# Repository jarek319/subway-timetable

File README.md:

# subway-timetable
A "Times Square" colorful LED display that shows you your favorite subway's status

Up to date info about your subway line and its arrival time for your station

I wanted to use one of those super colorful 32 x 64 RGB LED "times square" modules to display the subway schedule of the train nearest to me.

Still a work in progress, but the hardware is ready and the firmware works :)

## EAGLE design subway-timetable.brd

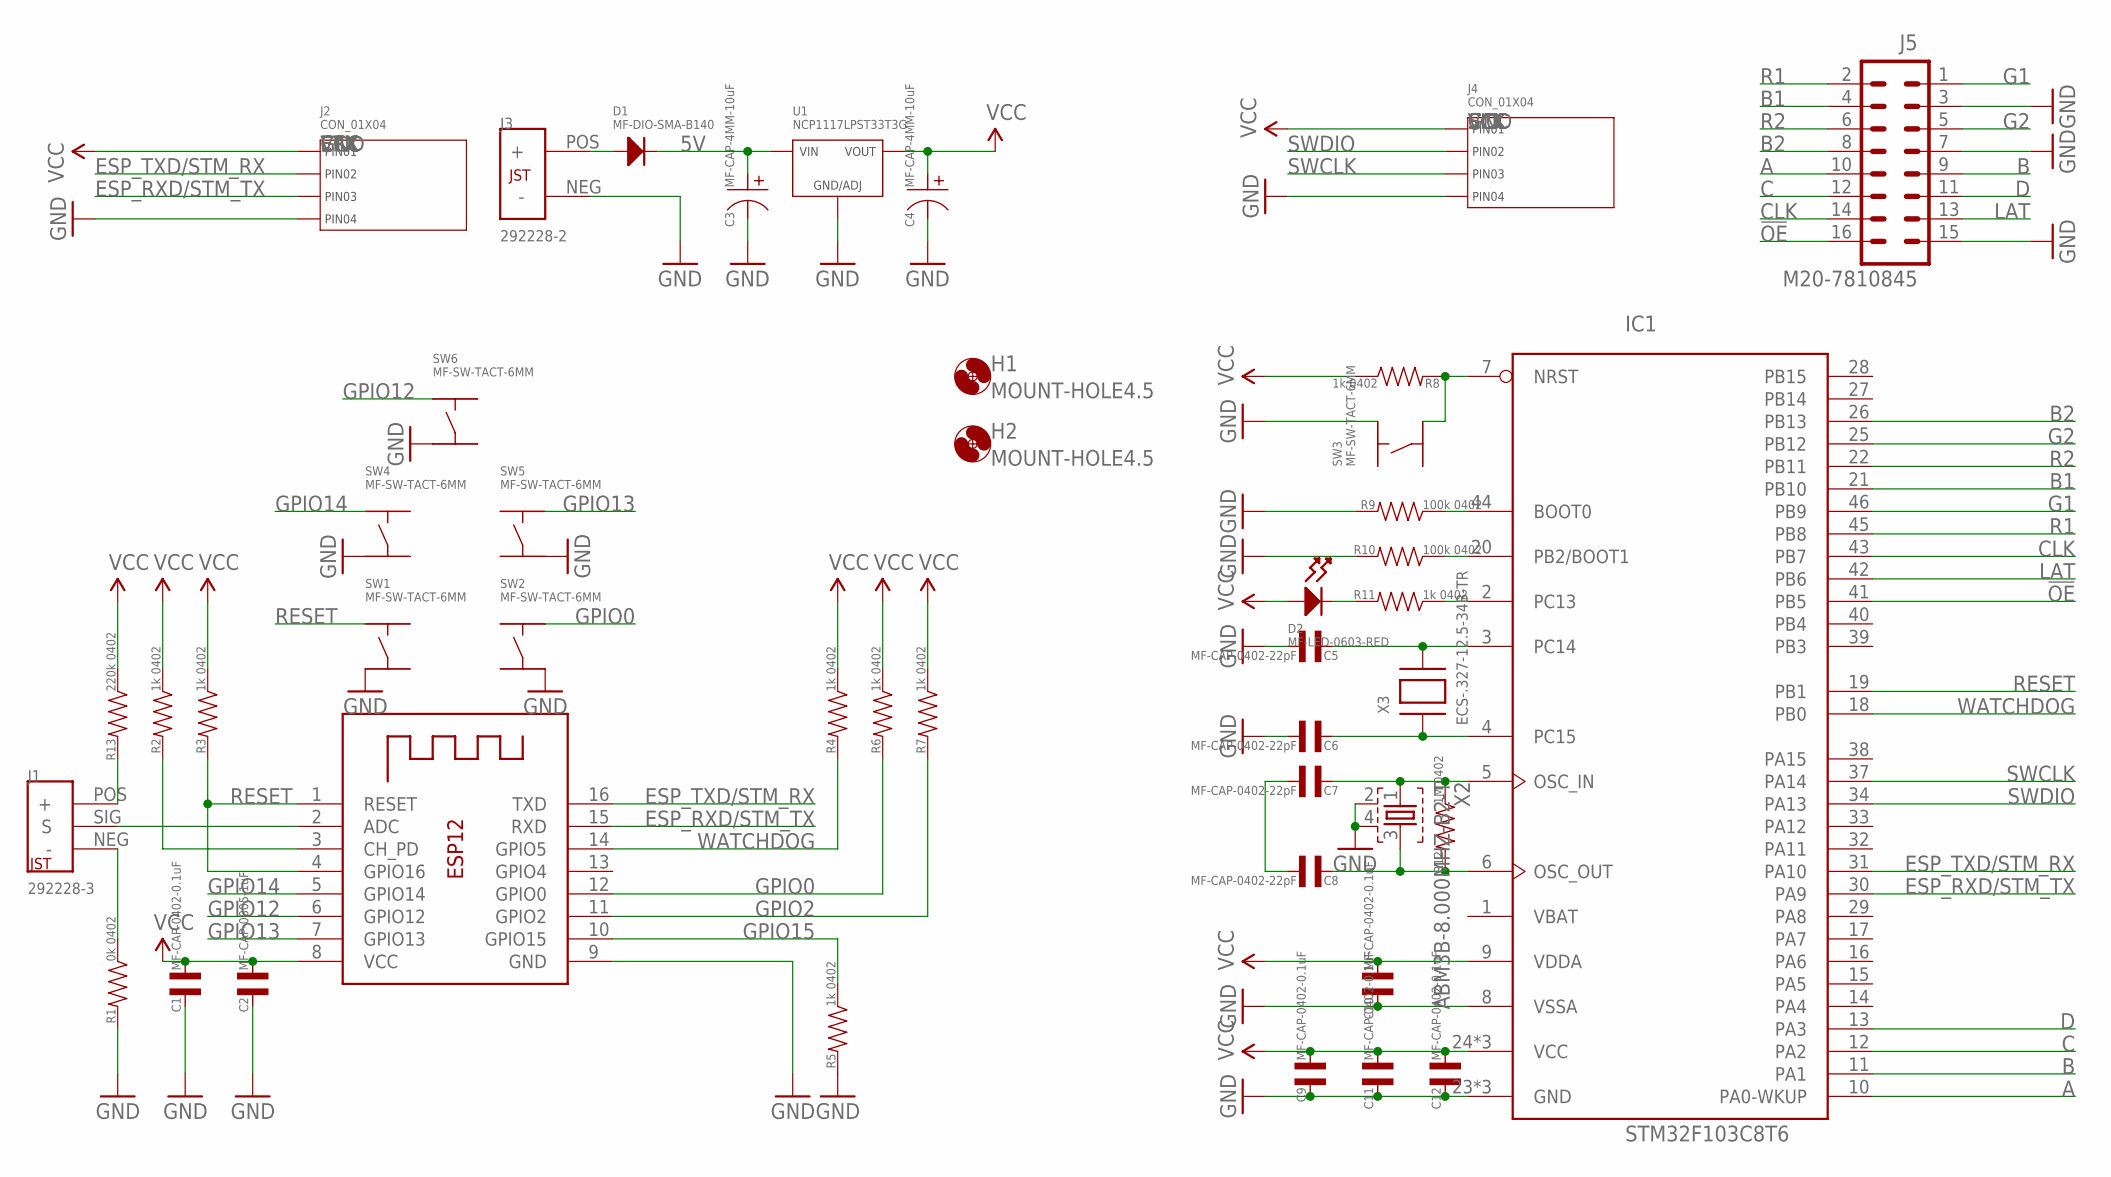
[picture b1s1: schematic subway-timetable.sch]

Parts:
C1, C9, C10, C11, C12: MF-CAP-0402-0.1uF; C0402
C2: MF-CAP-0805-1uF; C0805
C3, C4: MF-CAP-4MM-10uF; CP4MM
C5, C6, C7, C8: MF-CAP-0402-22pF; C0402
D1: MF-DIO-SMA-B140; SMA
D2: MF-LED-0603-RED; LED0603
H1, H2: MOUNT-HOLE4.5; 4,5
IC1: STM32F103C8T6; LQFP48
J1: 292228-3
J2, J4: CON_01X04; PTH_2.54MM_01X04_SPECIAL
J3: 292228-2
J5: M20-7810845; 2X8_SMD
R1: 0k 0402; R0402
R2, R3, R4, R5, R6, R7, R8, R11: 1k 0402; R0402
R9, R10: 100k 0402; R0402
R12: 1M 0402; R0402
R13: 220k 0402; R0402
SW1, SW2, SW3, SW4, SW5, SW6: MF-SW-TACT-6MM; TACT6MM
U1: NCP1117LPST33T3G; SOT-223-3
X1: ESP-12
X2: ABM3B-8.000MHZ-B2-T; 5.2X3.4-4-PAD
X3: ECS-.327-12.5-34B-TR; XTAL3215

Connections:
5V: C3.P$1, D1.CATHODE, U1.P$4 (VIN)
!OE: IC1.41 (PB5), J5.16
A: IC1.10 (PA0-WKUP), J5.10
B: IC1.11 (PA1), J5.9
B1: IC1.21 (PB10), J5.4
B2: IC1.26 (PB13), J5.8
C: IC1.12 (PA2), J5.12
CLK: IC1.43 (PB7), J5.14
D: IC1.13 (PA3), J5.11
ESP_RXD/STM_TX: IC1.30 (PA9), J2.P$3 (PIN3), X1.15 (RXD)
ESP_TXD/STM_RX: IC1.31 (PA10), J2.P$2 (PIN2), X1.16 (TXD)
G1: IC1.46 (PB9), J5.1
G2: IC1.25 (PB12), J5.5
GND: C1.P$2, C2.P$2, C3.P$2, C4.P$2, C5.P$1, C6.P$1, C9.P$2, C10.P$2, C11.P$2, C12.P$2, IC1.8 (VSSA), IC1.23 (GND), IC1.35 (GND), IC1.47 (GND), J2.P$4 (PIN4), J3.NEG (-), J4.P$4 (PIN4), J5.3, J5.7, J5.15, R1.P$2, R5.P$2, R9.P$2, R10.P$2, SW1.P$3, SW2.P$4, SW3.P$2, SW4.P$3, SW5.P$4, SW6.P$3, U1.P$2 (GND/ADJ), X1.9 (GND), X2.2, X2.4
GPIO0: R6.P$2, SW2.P$2, X1.12 (GPIO0)
GPIO2: R7.P$2, X1.11 (GPIO2)
GPIO12: SW6.P$1, X1.6 (GPIO12)
GPIO13: SW5.P$2, X1.7 (GPIO13)
GPIO14: SW4.P$1, X1.5 (GPIO14)
GPIO15: R5.P$1, X1.10 (GPIO15)
LAT: IC1.42 (PB6), J5.13
unnamed: IC1.20 (PB2/BOOT1), R10.P$1
unnamed: R2.P$2, X1.3 (CH_PD)
unnamed: D2.CATHODE, R11.P$2
unnamed: IC1.7 (NRST), R8.P$2, SW3.P$4
unnamed: IC1.44 (BOOT0), R9.P$1
unnamed: J1.SIG (S), X1.2 (ADC)
unnamed: IC1.2 (PC13), R11.P$1
unnamed: C5.P$2, IC1.3 (PC14), X3.P$2
unnamed: C6.P$2, IC1.4 (PC15), X3.P$1
unnamed: C7.P$2, IC1.5 (OSC_IN), R12.P$1, X2.1
unnamed: C8.P$2, IC1.6 (OSC_OUT), R12.P$2, X2.3
unnamed: C7.P$1, C8.P$1
unnamed: D1.ANODE, J3.POS (+)
unnamed: J1.NEG (-), R1.P$1
unnamed: J1.POS (+), R13.P$2
R1: IC1.45 (PB8), J5.2
R2: IC1.22 (PB11), J5.6
RESET: IC1.19 (PB1), R3.P$2, SW1.P$1, X1.1 (RESET), X1.4 (GPIO16)
SWCLK: IC1.37 (PA14), J4.P$3 (PIN3)
SWDIO: IC1.34 (PA13), J4.P$2 (PIN2)
VBAT: IC1.1 (VBAT)
VCC: C1.P$1, C2.P$1, C4.P$1, C9.P$1, C10.P$1, C11.P$1, C12.P$1, D2.ANODE, IC1.9 (VDDA), IC1.24 (VCC), IC1.36 (VCC), IC1.48 (VCC), J2.P$1 (PIN1), J4.P$1 (PIN1), R2.P$1, R3.P$1, R4.P$1, R6.P$1, R7.P$1, R8.P$1, R13.P$1, U1.P$1 (VOUT), U1.P$3 (VOUT), X1.8 (VCC)
WATCHDOG: IC1.18 (PB0), R4.P$2, X1.14 (GPIO5)

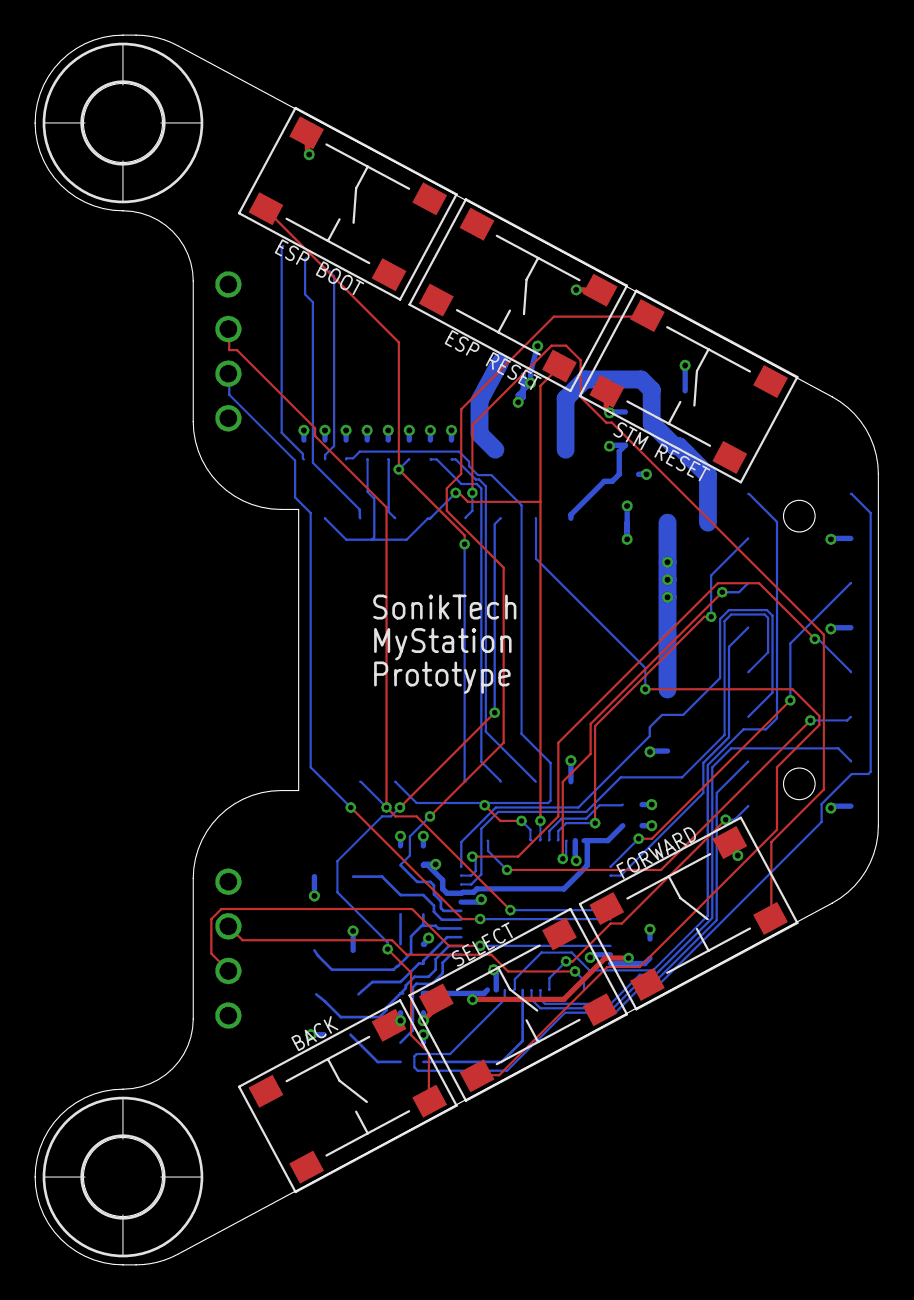
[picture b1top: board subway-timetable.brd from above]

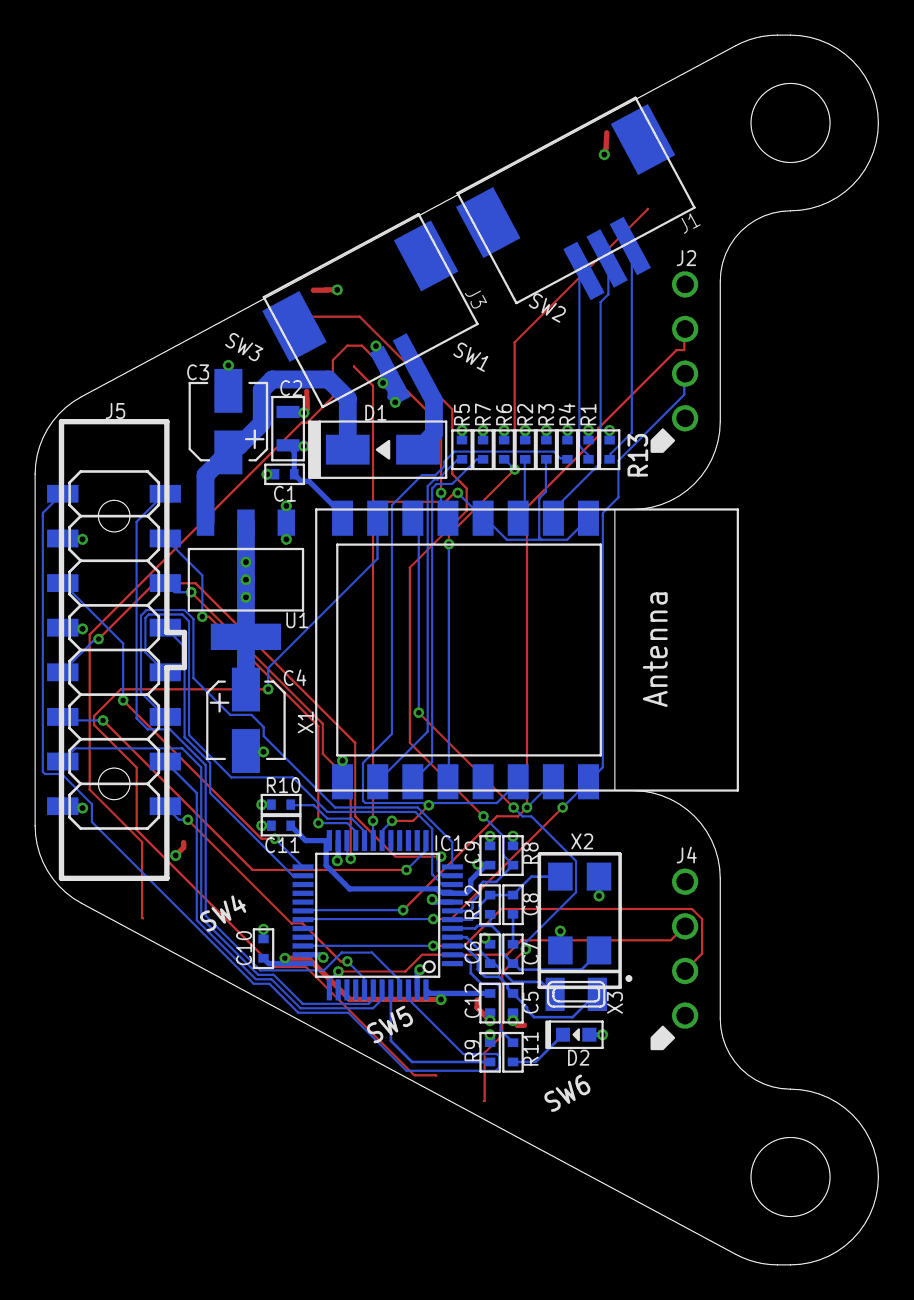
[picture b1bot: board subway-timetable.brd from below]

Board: 4 copper layers, 48.0 x 70.0 mm, 45 parts (35 on the bottom side), 43 nets.

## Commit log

2018-07-05 design tested: working

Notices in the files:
parts and their libraries:
SparkFun-Connectors: Licensing: Creative Commons ShareAlike 4.0 International - https://creativecommons.org/licenses/by-sa/4.0
